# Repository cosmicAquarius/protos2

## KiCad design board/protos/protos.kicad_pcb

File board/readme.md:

## KiCad Footprints

This project uses the `NodeMCU1.0(12-E)` footprint, which is **not included** in the repository.

To avoid errors:
- Make sure KiCad can access the `NodeMCU1.0(12-E).kicad_mod` library
- Or install it manually from a public repository (e.g. https://github.com/LoathingKernel/kicad-nodemcu)

compact level shifter
https://www.youtube.com/watch?v=hvf990VPiRg

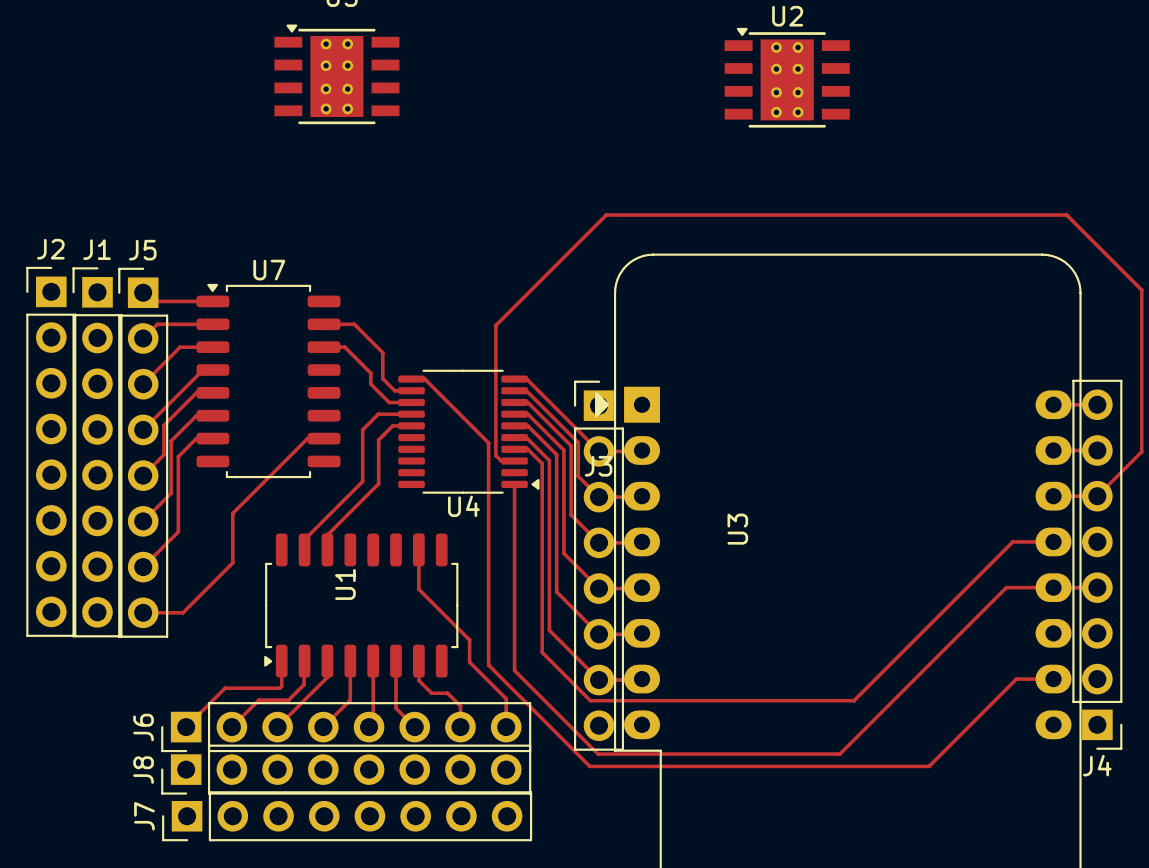
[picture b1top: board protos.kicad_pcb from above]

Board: 2 copper layers, 14 parts (0 on the bottom side), 35 nets.

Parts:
J1, J2, J3, J4, J5, J6, J7, J8: Conn_01x08_Pin; PinHeader_1x08_P2.54mm_Vertical
U1, U7: 4017; SOP-16_4.4x10.4mm_P1.27mm
U2, U5: TPS5430DDA; TI_SO-PowerPAD-8_ThermalVias
U3: WEMOS_D1_mini; WEMOS_D1_mini_light
U4: TXS0108EPW; TSSOP-20_4.4x6.5mm_P0.65mm

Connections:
GND: U3.10 (GND), U4.11 (GND)
unnamed: J3.2, U3.2 (A0), U4.10 (OE)
unnamed: J3.3, U3.3 (D0), U4.9 (A8)
unnamed: J3.4, U3.4 (SCK/D5), U4.8 (A7)
unnamed: J3.5, U3.5 (MISO/D6), U4.7 (A6)
unnamed: J3.6, U3.6 (MOSI/D7), U4.6 (A5)
unnamed: J3.7, U3.7 (CS/D8), U4.5 (A4)
unnamed: J3.8, U3.8 (3V3)
unnamed: J4.2, U3.9 (5V)
unnamed: J4.3, U3.11 (D4)
unnamed: J4.4, U3.12 (D3), U4.1 (A1)
unnamed: J4.5, U3.13 (SDA/D2), U4.4 (A3)
unnamed: J4.6, U3.14 (SCL/D1), U4.3 (A2)
unnamed: J4.7, U3.15 (RX)
unnamed: J4.8, U3.16 (TX)
unnamed: J5.1, U7.1 (Q5)
unnamed: J5.2, U7.2 (Q1)
unnamed: J5.3, U7.3 (Q0)
unnamed: J5.4, U7.4 (Q2)
unnamed: J5.5, U7.5 (Q6)
unnamed: J5.6, U7.6 (Q7)
unnamed: J5.7, U7.7 (Q3)
unnamed: J5.8, U7.10 (Q4)
unnamed: J6.1, U1.1 (Q5)
unnamed: J6.2, U1.2 (Q1)
unnamed: J6.3, U1.3 (Q0)
unnamed: J6.4, U1.4 (Q2)
unnamed: J6.5, U1.5 (Q6)
unnamed: J6.6, U1.6 (Q7)
unnamed: J6.7, U1.7 (Q3)
unnamed: J6.8, U1.10 (Q4)
unnamed: U1.14 (CLK), U4.15 (B5)
unnamed: U1.15 (Reset), U4.14 (B6)
unnamed: U4.13 (B7), U7.14 (CLK)
unnamed: U4.12 (B8), U7.15 (Reset)

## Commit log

2025-05-11 change licence
